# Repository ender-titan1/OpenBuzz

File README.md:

# OpenBuzz
OpenBuzz is a free and open source buzzer system for trivia games & tournaments, gameshows, or any competition where timing matters. It can be used with 2 teams of up to 4 players or with up to 8 independent players.

## Features
- Open source 
- Fully hand-solderable
- Modular and modifyable
- Designed to be fabricated as cheaply as possible
- Support for extensive customization, many game modes and a wide range of buzzer sounds
- Use of common RJ45 connector for easy and cheap connection between base and pods

## Why make this?
Professional buzzer systems tend to be very expensive and not very customizable, as well as being tricky to obtain due to overseas shipping. OpenBuzz aims to provide a cheaper and more flexible alternative, while maintaining fairness and accurate winner detection. It was originally designed for a local trivia team that needed a system to practice with, but since has been made open source. As a bonus it allows players to have their own custom buzzers, ranging from simple buttons to way over-the-top triggers.

# Usage
1. Download schematic and PCB files
2. Modify freely to fit your needs, components, etc...
3. Fabricate with any online service for as little as <$10
4. Assemble base and as many pods as you need
5. 3D-print enclosures if needed
6. Use in any game you need it for!

**Disclaimer: V1 is included in this repository for historical reference only. Versions V2 and above are the ones intended for use.**

PCB files and schematics are provided as KiCad files. 3D files for enclosures are provided as STEP files.

# License
The code and firmware included in the `src` folder is covered by the GNU General Public License v3.0, while the design files (schematics, PCB layout, 3D models) in the `hardware` folder are covered by the CERN Open Hardware Licence Version 2 - Strongly Reciprocal license. The full license texts can be found in their respective folders.

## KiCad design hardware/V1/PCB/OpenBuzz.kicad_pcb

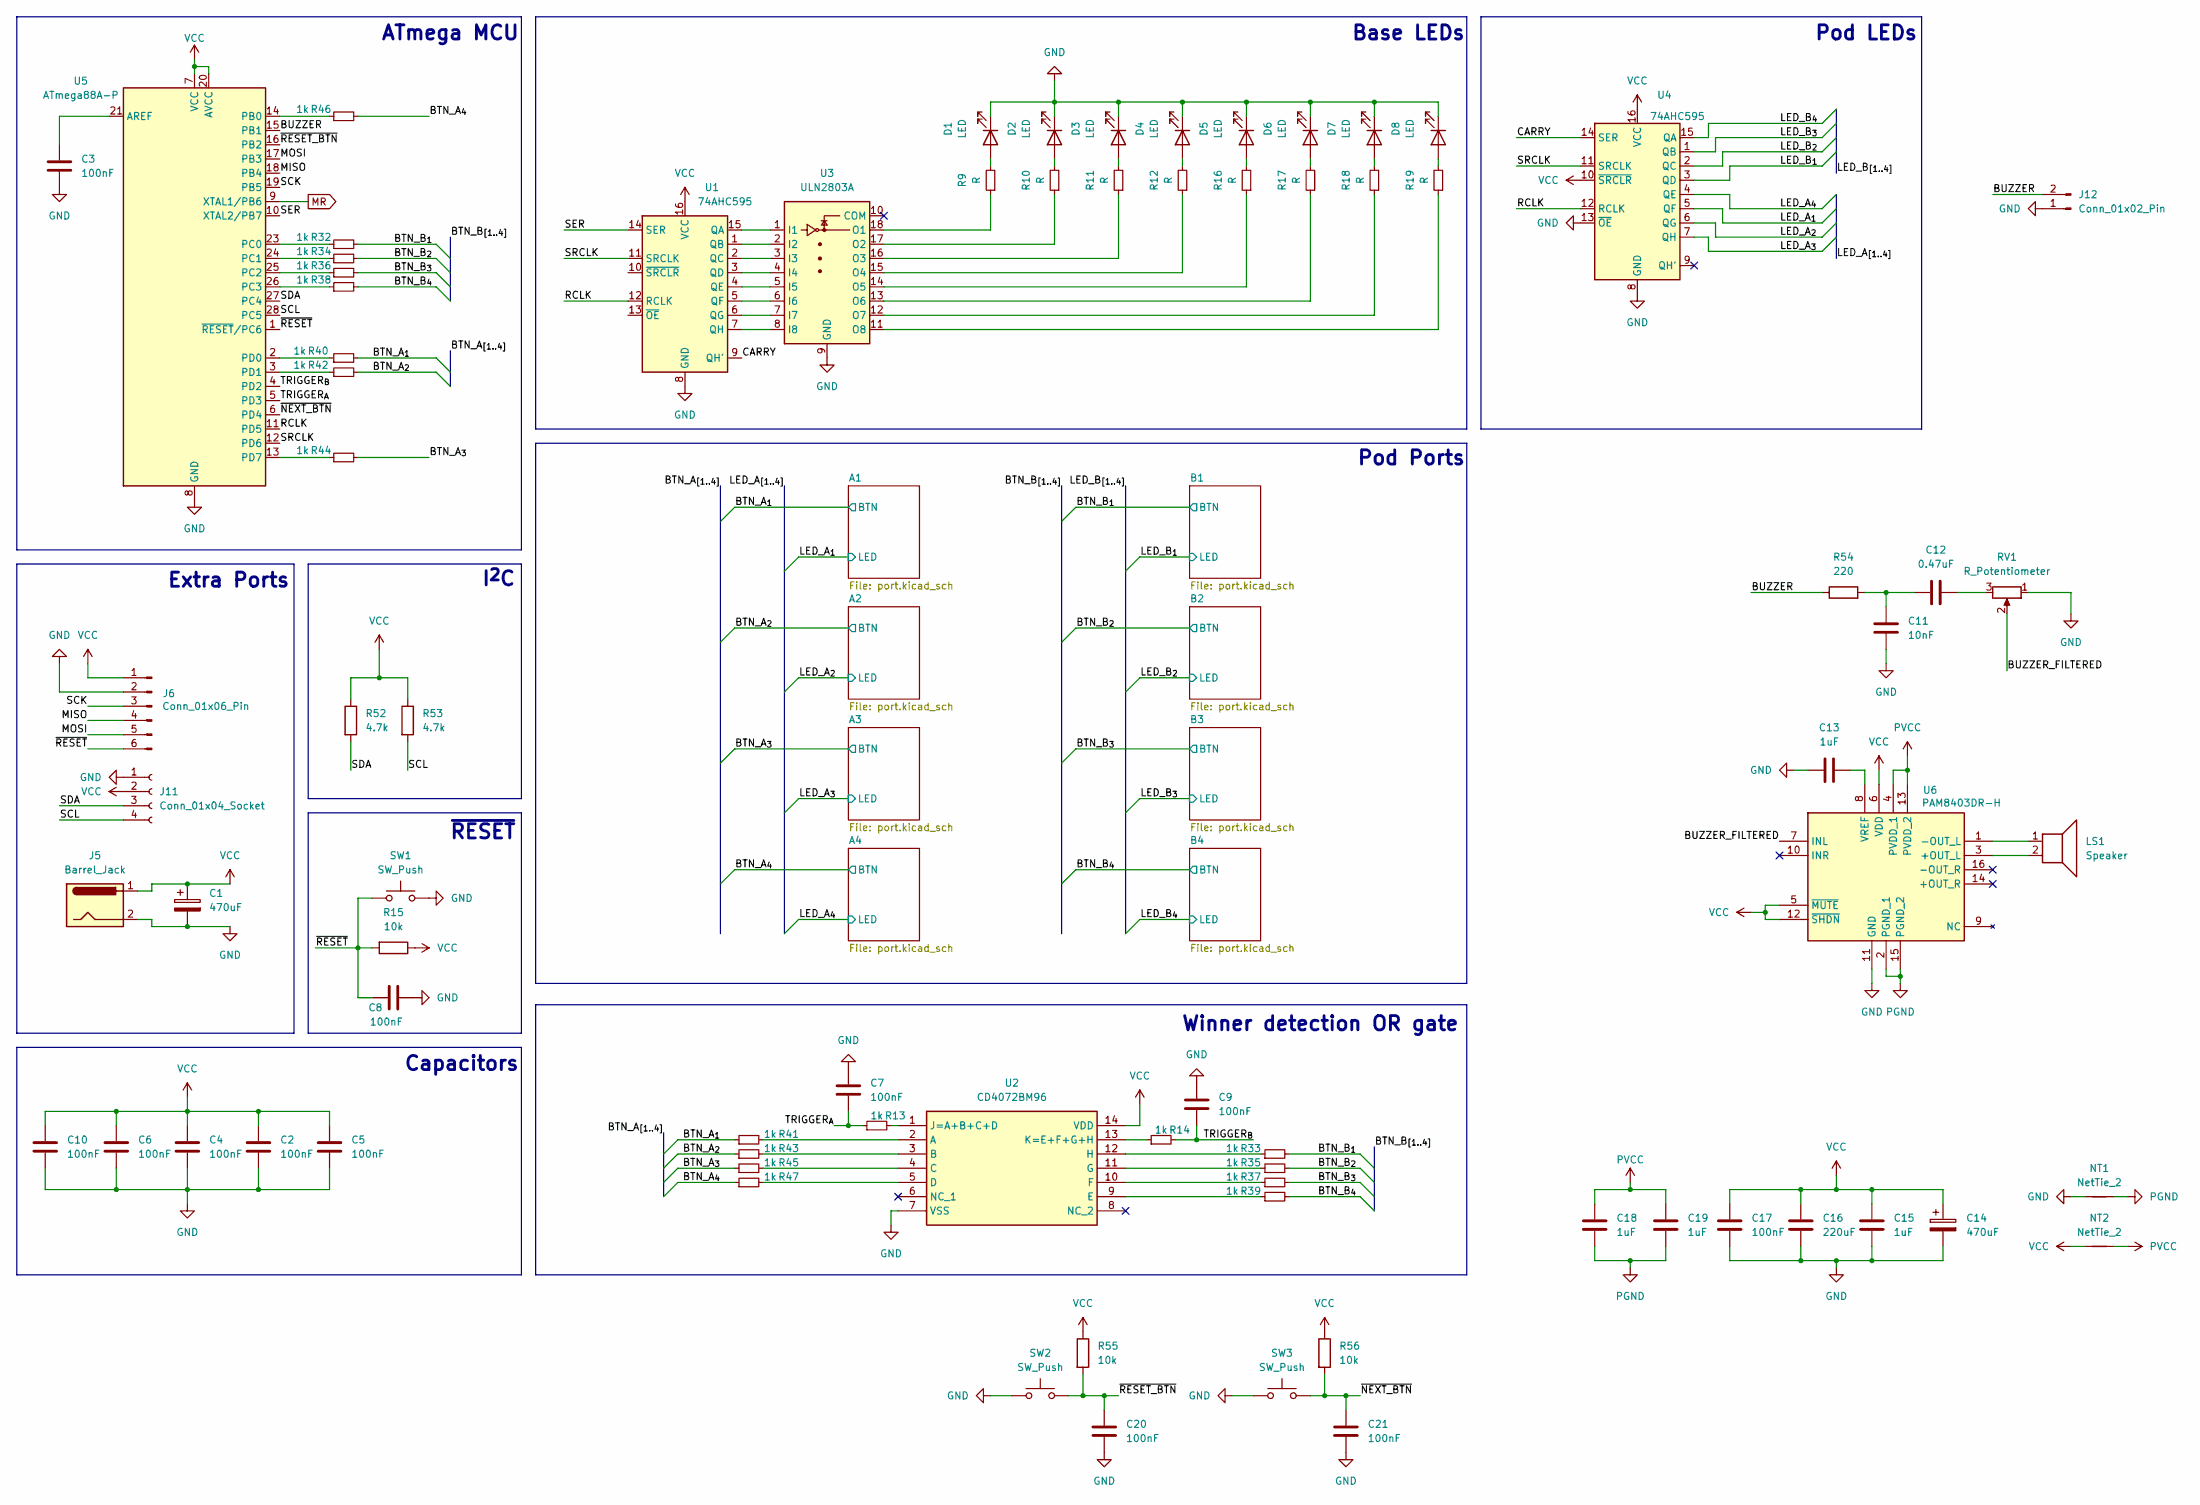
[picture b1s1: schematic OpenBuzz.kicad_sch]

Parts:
C1, C14: 470uF; CP_Radial_D8.0mm_P3.50mm
C2, C3, C4, C5, C6, C7, C8, C9, C10, C17, C20, C21: 100nF; C_0805_2012Metric_Pad1.18x1.45mm_HandSolder
C11: 10nF; C_0805_2012Metric_Pad1.18x1.45mm_HandSolder
C12: 0.47uF; C_0805_2012Metric_Pad1.18x1.45mm_HandSolder
C13, C15, C18, C19: 1uF; C_0805_2012Metric_Pad1.18x1.45mm_HandSolder
C16: 220uF; C_0805_2012Metric_Pad1.18x1.45mm_HandSolder
D1, D2, D3, D4, D5, D6, D7, D8: LED; LED_D5.0mm
J5: Barrel_Jack; BarrelJack_Horizontal
J6: Conn_01x06_Pin; PinHeader_1x06_P2.54mm_Vertical
J11: Conn_01x04_Socket; NS-Tech_Grove_1x04_P2mm_Vertical
J12: Conn_01x02_Pin; PinHeader_1x02_P2.54mm_Vertical
LS1: Speaker; PinHeader_1x02_P2.54mm_Vertical
NT1, NT2: NetTie_2; NetTie-2_SMD_Pad2.0mm
R9, R10, R11, R12, R16, R17, R18, R19: R; R_0805_2012Metric_Pad1.20x1.40mm_HandSolder
R13, R14, R32, R33, R34, R35, R36, R37, R38, R39, R40, R41, R42, R43, R44, R45, R46, R47: 1k; R_0805_2012Metric_Pad1.20x1.40mm_HandSolder
R15, R55, R56: 10k; R_0805_2012Metric_Pad1.20x1.40mm_HandSolder
R52, R53: 4.7k; R_0805_2012Metric_Pad1.20x1.40mm_HandSolder
R54: 220; R_0805_2012Metric_Pad1.20x1.40mm_HandSolder
RV1: R_Potentiometer; PinHeader_1x03_P2.54mm_Vertical
SW1: SW_Push; SW_Push_1P1T_NO_CK_KSC6xxJ
SW2, SW3: SW_Push; PinHeader_1x02_P2.54mm_Vertical
U1, U4: 74AHC595; DIP-16_W7.62mm_Socket_LongPads
U2: CD4072BM96; SOIC-14_3.9x8.7mm_P1.27mm; Mouser Part Number 595-CD4072BE
U3: ULN2803A; DIP-18_W7.62mm_Socket_LongPads
U5: ATmega88A-P; DIP-28_W7.62mm_Socket_LongPads
U6: PAM8403DR-H; SOIC-16_3.9x9.9mm_P1.27mm; Manufacturer_Part_Number PAM8403DR-H

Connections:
/BTN_A_{1}: R40.2, R41.1; also elsewhere on the board
/BTN_A_{2}: R42.2, R43.1; also elsewhere on the board
/BTN_A_{3}: R44.2, R45.1; also elsewhere on the board
/BTN_A_{4}: R46.2, R47.1; also elsewhere on the board
/BTN_B_{1}: R32.2, R33.2; also elsewhere on the board
/BTN_B_{2}: R34.2, R35.2; also elsewhere on the board
/BTN_B_{3}: R36.2, R37.2; also elsewhere on the board
/BTN_B_{4}: R38.2, R39.2; also elsewhere on the board
/BUZZER: J12.2, R54.1, U5.15 (PB1)
/BUZZER_FILTERED: RV1.2, U6.7 (INL)
/CARRY: U1.9 (QH'), U4.14 (SER)
/LED_A_{1}: U4.5 (QF); also elsewhere on the board
/LED_A_{2}: U4.6 (QG); also elsewhere on the board
/LED_A_{3}: U4.7 (QH); also elsewhere on the board
/LED_A_{4}: U4.4 (QE); also elsewhere on the board
/LED_B_{1}: U4.3 (QD); also elsewhere on the board
/LED_B_{2}: U4.2 (QC); also elsewhere on the board
/LED_B_{3}: U4.1 (QB); also elsewhere on the board
/LED_B_{4}: U4.15 (QA); also elsewhere on the board
/MISO: J6.4, U5.18 (PB4)
/MOSI: J6.5, U5.17 (PB3)
/RCLK: U1.12 (RCLK), U4.12 (RCLK), U5.11 (PD5)
/SCK: J6.3, U5.19 (PB5)
/SCL: J11.4, R53.2, U5.28 (PC5)
/SDA: J11.3, R52.2, U5.27 (PC4)
/SER: U1.14 (SER), U5.10 (XTAL2/PB7)
/SRCLK: U1.11 (SRCLK), U4.11 (SRCLK), U5.12 (PD6)
/TRIGGER_{A}: C7.2, R13.1, U5.5 (PD3)
/TRIGGER_{B}: C9.2, R14.2, U5.4 (PD2)
/~NEXT_BTN: C21.1, R56.2, SW3.2, U5.6 (PD4)
/~RESET_BTN: C20.1, R55.2, SW2.2, U5.16 (PB2)
/~RESET: C8.2, J6.6, R15.2, SW1.1, U5.1 (~RESET/PC6)
GND: C1.2, C2.2, C3.2, C4.2, C5.2, C6.2, C7.1, C8.1, C9.1, C10.2, C11.2, C13.1, C14.2, C15.2, C16.2, C17.2, C20.2, C21.2, D1.1 (K), D2.1 (K), D3.1 (K), D4.1 (K), D5.1 (K), D6.1 (K), D7.1 (K), D8.1 (K), J5.2, J6.2, J11.1, J12.1, NT1.1, RV1.1, SW1.2, SW2.1, SW3.1, U1.8 (GND), U2.7 (VSS), U3.9 (GND), U4.8 (GND), U4.13 (~OE), U5.8 (GND), U5.22 (GND), U6.11 (GND); also elsewhere on the board
MR: U5.9 (XTAL1/PB6); also elsewhere on the board
unnamed: C11.1, C12.1, R54.2
unnamed: C12.2, RV1.3
unnamed: D1.2 (A), R9.2
unnamed: D2.2 (A), R10.2
unnamed: D3.2 (A), R11.2
unnamed: D4.2 (A), R12.2
unnamed: D5.2 (A), R16.2
unnamed: D6.2 (A), R17.2
unnamed: D7.2 (A), R18.2
unnamed: D8.2 (A), R19.2
unnamed: U1.15 (QA), U3.1 (I1)
unnamed: U1.1 (QB), U3.2 (I2)
unnamed: U1.2 (QC), U3.3 (I3)
unnamed: U1.3 (QD), U3.4 (I4)
unnamed: U1.4 (QE), U3.5 (I5)
unnamed: U1.5 (QF), U3.6 (I6)
unnamed: U1.6 (QG), U3.7 (I7)
unnamed: U1.7 (QH), U3.8 (I8)
unnamed: R41.2, U2.2 (A)
unnamed: R43.2, U2.3 (B)
unnamed: R45.2, U2.4 (C)
unnamed: R47.2, U2.5 (D)
unnamed: R39.1, U2.9 (E)
unnamed: R37.1, U2.10 (F)
unnamed: R35.1, U2.11 (G)
unnamed: R33.1, U2.12 (H)
unnamed: R13.2, U2.1 (J=A+B+C+D)
unnamed: R14.1, U2.13 (K=E+F+G+H)
unnamed: R9.1, U3.18 (O1)
unnamed: R10.1, U3.17 (O2)
unnamed: R11.1, U3.16 (O3)
unnamed: R12.1, U3.15 (O4)
unnamed: R16.1, U3.14 (O5)
unnamed: R17.1, U3.13 (O6)
unnamed: R18.1, U3.12 (O7)
unnamed: R19.1, U3.11 (O8)
unnamed: C3.1, U5.21 (AREF)
unnamed: R46.1, U5.14 (PB0)
unnamed: R32.1, U5.23 (PC0)
unnamed: R34.1, U5.24 (PC1)
unnamed: R36.1, U5.25 (PC2)
unnamed: R38.1, U5.26 (PC3)
unnamed: R40.1, U5.2 (PD0)
unnamed: R42.1, U5.3 (PD1)
unnamed: R44.1, U5.13 (PD7)
unnamed: LS1.2, U6.3 (+OUT_L)
unnamed: LS1.1, U6.1 (-OUT_L)
unnamed: C13.2, U6.8 (VREF)
PGND: C18.2, C19.2, NT1.2, U6.2 (PGND_1), U6.15 (PGND_2)
PVCC: C18.1, C19.1, NT2.2, U6.4 (PVDD_1), U6.13 (PVDD_2)
VCC: C1.1, C2.1, C4.1, C5.1, C6.1, C10.1, C14.1, C15.1, C16.1, C17.1, J5.1, J6.1, J11.2, NT2.1, R15.1, R52.1, R53.1, R55.1, R56.1, U1.16 (VCC), U2.14 (VDD), U4.10 (~SRCLR), U4.16 (VCC), U5.7 (VCC), U5.20 (AVCC), U6.5 (~MUTE), U6.6 (VDD), U6.12 (~SHDN); also elsewhere on the board

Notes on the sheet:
Base LEDs
~{RESET}
Pod LEDs
ATmega MCU
Pod Ports
I^{2}C
Extra Ports
Capacitors
Winner detection OR gate

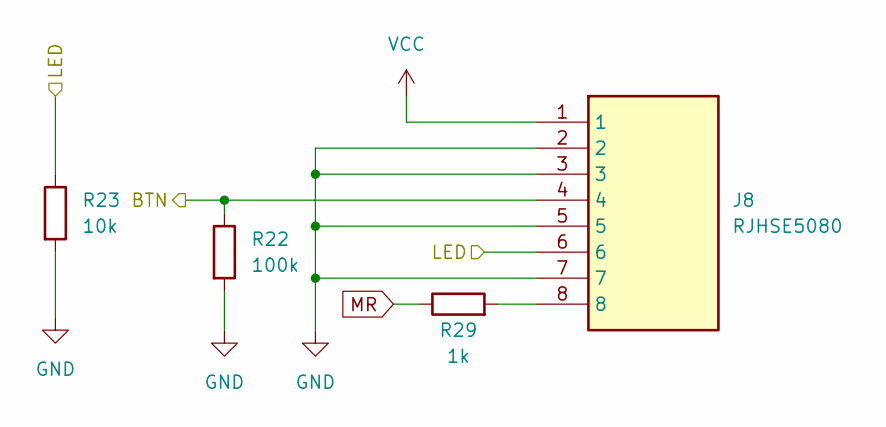
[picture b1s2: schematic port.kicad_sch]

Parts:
J8: RJHSE5080; Manufacturer_Part_Number RJHSE5080
R22: 100k; R_0805_2012Metric_Pad1.20x1.40mm_HandSolder
R23: 10k; R_0805_2012Metric_Pad1.20x1.40mm_HandSolder
R29: 1k; R_0805_2012Metric_Pad1.20x1.40mm_HandSolder

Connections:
/BTN_B_{2}: J8.4, R22.1; also elsewhere on the board
/LED_B_{2}: J8.6, R23.1; also elsewhere on the board
GND: J8.2, J8.3, J8.5, J8.7, R22.2, R23.2; also elsewhere on the board
MR: R29.1; also elsewhere on the board
unnamed: J8.8, R29.2
VCC: J8.1; also elsewhere on the board

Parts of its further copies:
J1, J2, J3, J4, J7, J9, J10: RJHSE5080; Manufacturer_Part_Number RJHSE5080
R1, R3, R5, R7, R21, R25, R27: 10k; R_0805_2012Metric_Pad1.20x1.40mm_HandSolder
R2, R4, R6, R8, R20, R24, R26: 100k; R_0805_2012Metric_Pad1.20x1.40mm_HandSolder
R28, R30, R31, R48, R49, R50, R51: 1k; R_0805_2012Metric_Pad1.20x1.40mm_HandSolder

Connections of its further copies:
/BTN_A_{1}: J1.4, R2.1; also elsewhere on the board
/BTN_A_{2}: J2.4, R4.1; also elsewhere on the board
/BTN_A_{3}: J3.4, R6.1; also elsewhere on the board
/BTN_A_{4}: J4.4, R8.1; also elsewhere on the board
/BTN_B_{1}: J7.4, R20.1; also elsewhere on the board
/BTN_B_{3}: J9.4, R24.1; also elsewhere on the board
/BTN_B_{4}: J10.4, R26.1; also elsewhere on the board
/LED_A_{1}: J1.6, R1.1; also elsewhere on the board
/LED_A_{2}: J2.6, R3.1; also elsewhere on the board
/LED_A_{3}: J3.6, R5.1; also elsewhere on the board
/LED_A_{4}: J4.6, R7.1; also elsewhere on the board
/LED_B_{1}: J7.6, R21.1; also elsewhere on the board
/LED_B_{3}: J9.6, R25.1; also elsewhere on the board
/LED_B_{4}: J10.6, R27.1; also elsewhere on the board
GND: J1.2, J1.3, J1.5, J1.7, J2.2, J2.3, J2.5, J2.7, J3.2, J3.3, J3.5, J3.7, J4.2, J4.3, J4.5, J4.7, J7.2, J7.3, J7.5, J7.7, J9.2, J9.3, J9.5, J9.7, J10.2, J10.3, J10.5, J10.7, R1.2, R2.2, R3.2, R4.2, R5.2, R6.2, R7.2, R8.2, R20.2, R21.2, R24.2, R25.2, R26.2, R27.2; also elsewhere on the board
MR: R28.1, R30.1, R31.1, R48.1, R49.1, R50.1, R51.1; also elsewhere on the board
unnamed: J1.8, R48.2
unnamed: J2.8, R49.2
unnamed: J3.8, R50.2
unnamed: J4.8, R51.2
unnamed: J7.8, R28.2
unnamed: J9.8, R30.2
unnamed: J10.8, R31.2
VCC: J1.1, J2.1, J3.1, J4.1, J7.1, J9.1, J10.1; also elsewhere on the board

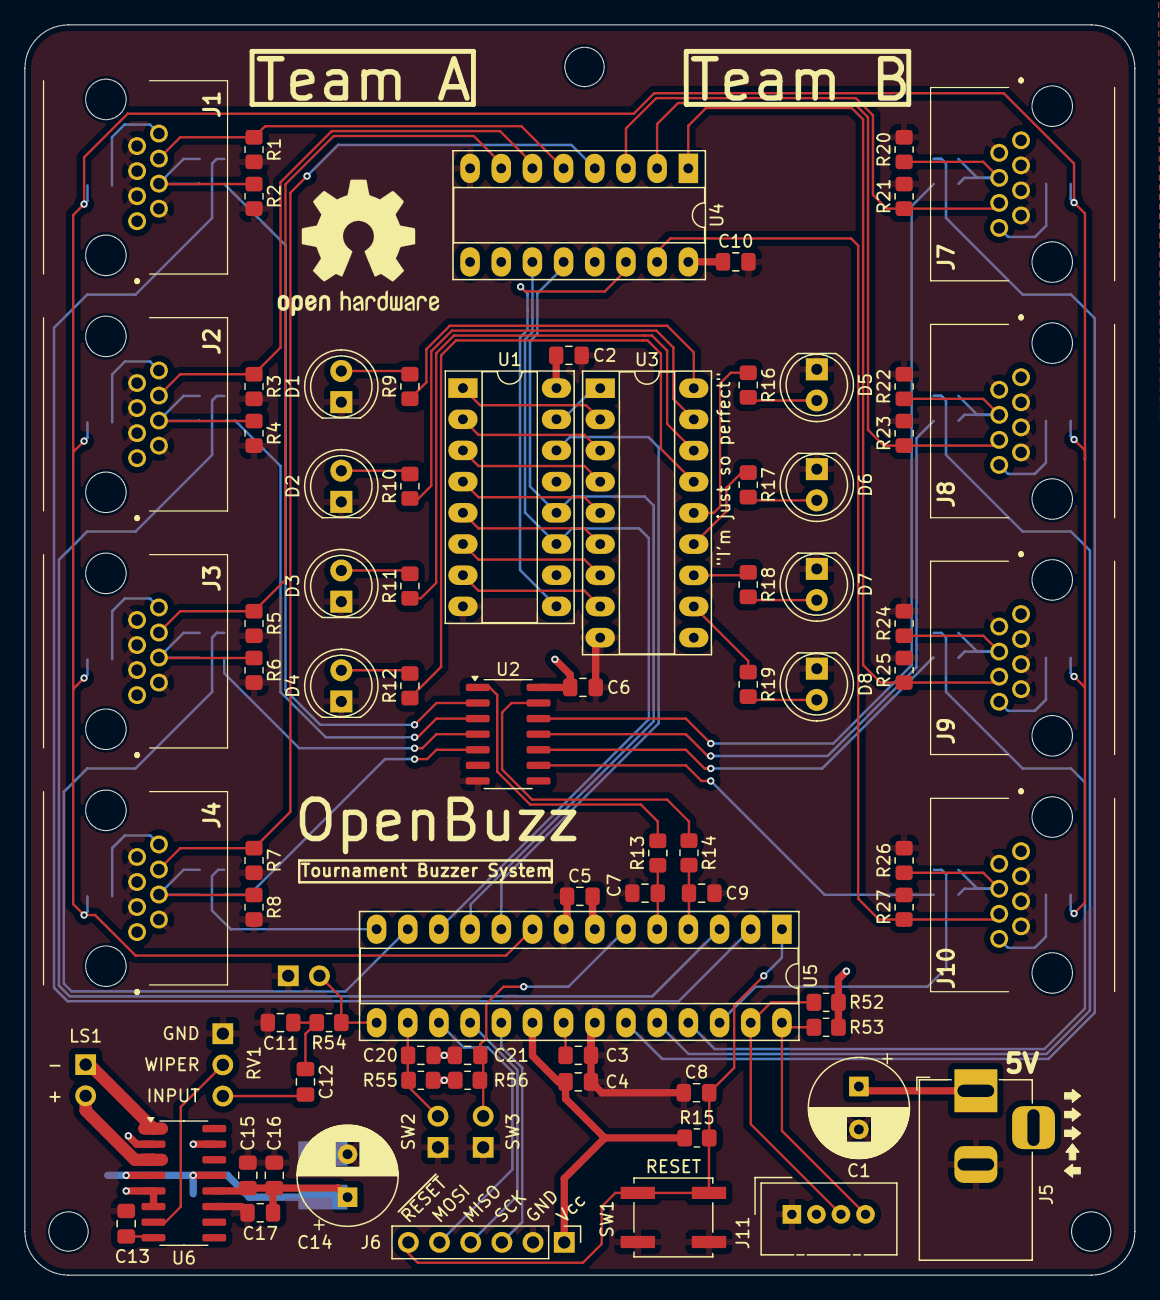
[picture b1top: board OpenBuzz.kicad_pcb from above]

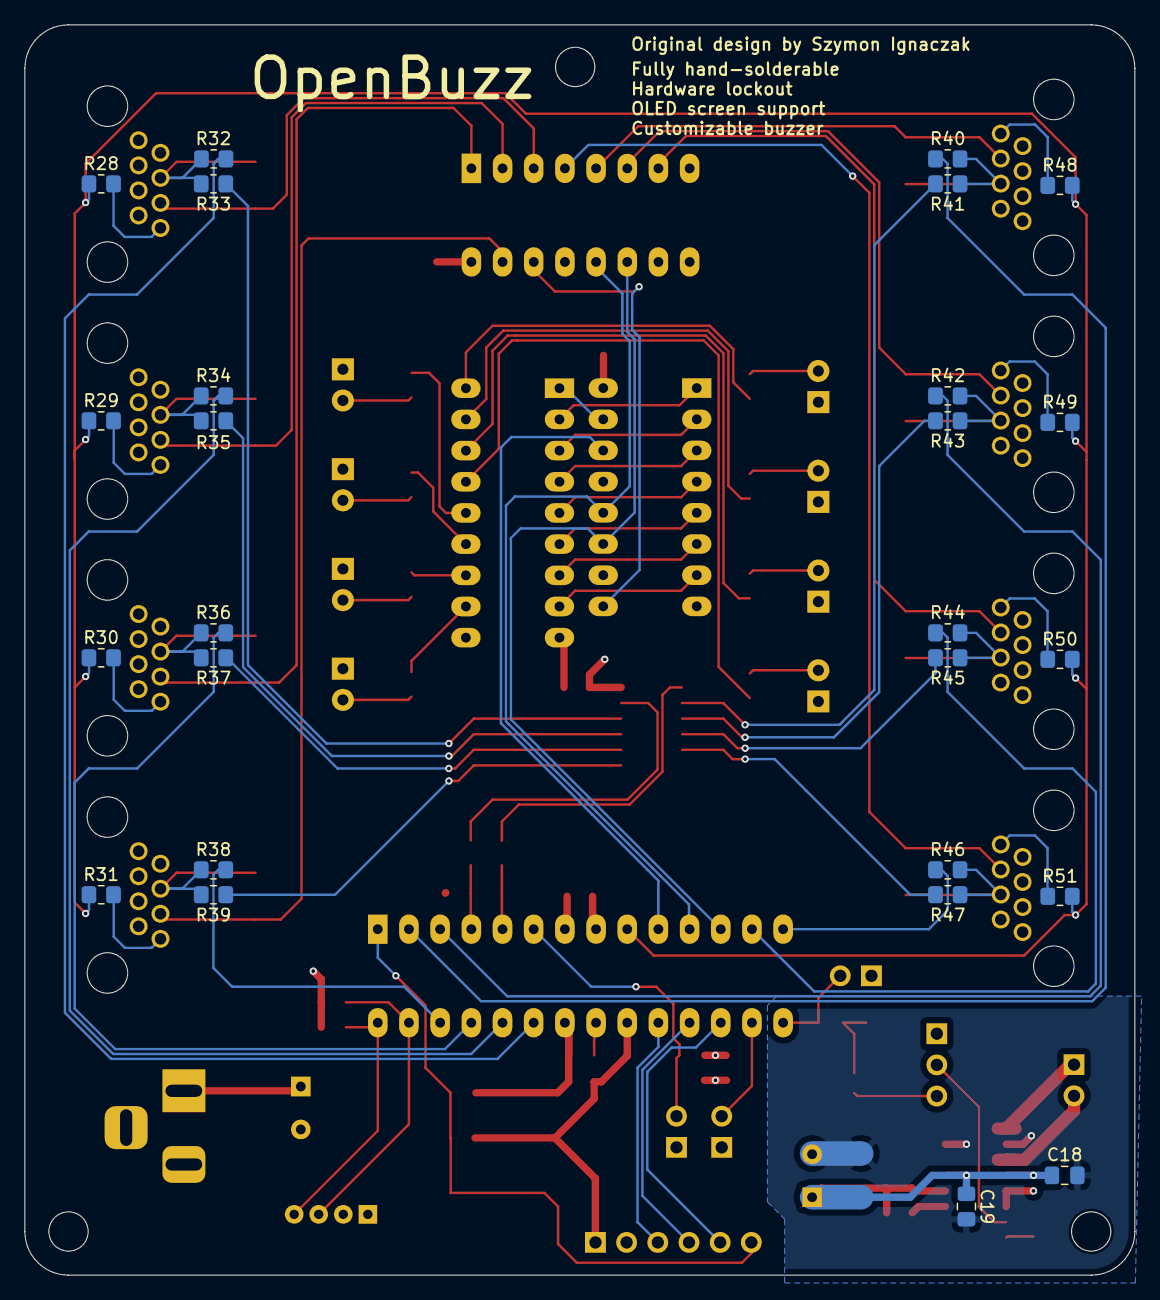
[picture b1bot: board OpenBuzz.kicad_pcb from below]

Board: 4 copper layers, 90.4 x 101.9 mm, 110 parts (28 on the bottom side), 93 nets.

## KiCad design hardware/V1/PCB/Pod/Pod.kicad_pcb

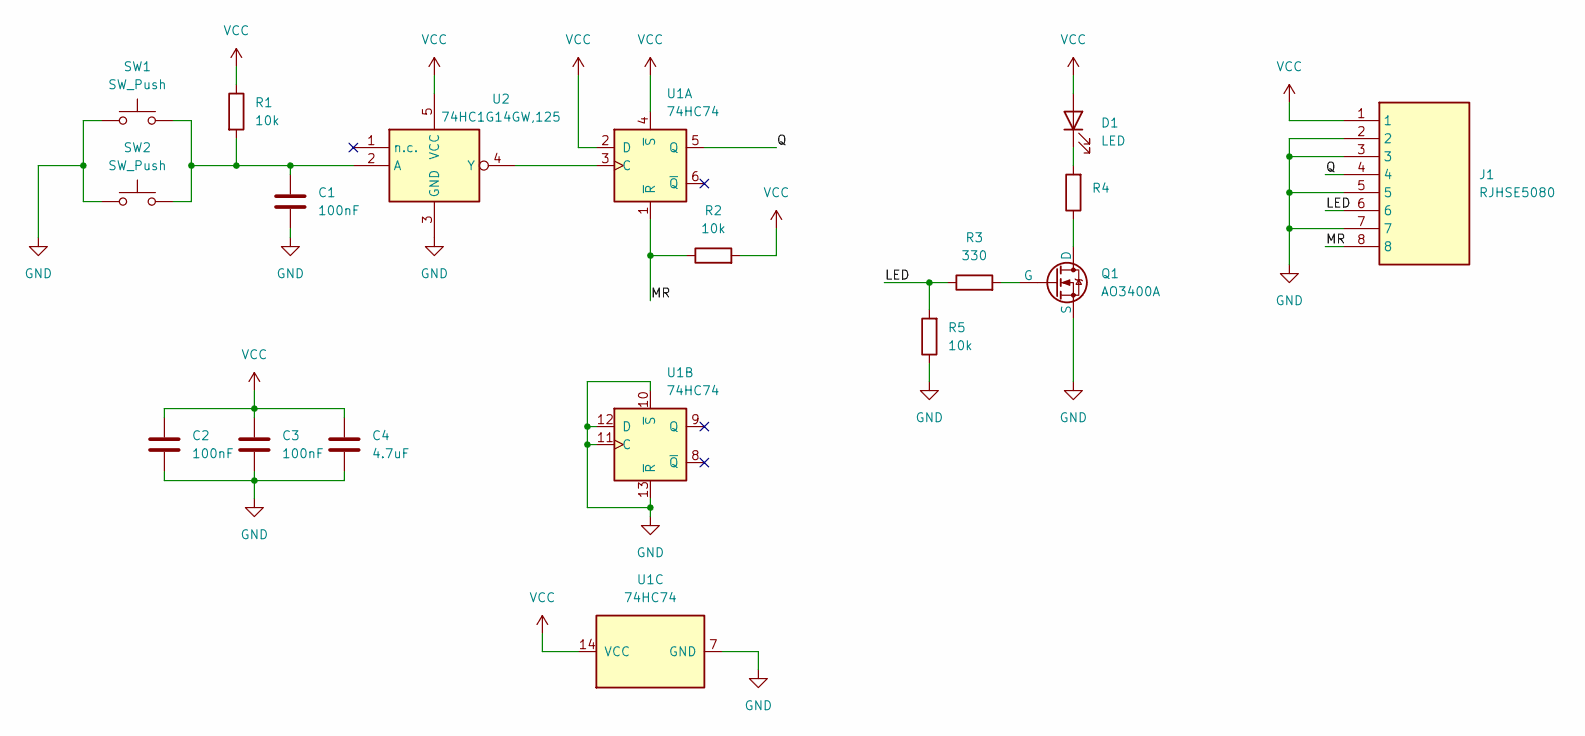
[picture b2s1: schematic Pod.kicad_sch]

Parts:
C1, C2, C3: 100nF; C_0805_2012Metric_Pad1.18x1.45mm_HandSolder
C4: 4.7uF; C_0805_2012Metric_Pad1.18x1.45mm_HandSolder
D1: LED; LED_D5.0mm
J1: RJHSE5080; Manufacturer_Part_Number RJHSE5080
Q1: AO3400A; SOT-23_Handsoldering
R1, R2, R5: 10k; R_0805_2012Metric_Pad1.20x1.40mm_HandSolder
R3: 330; R_0805_2012Metric_Pad1.20x1.40mm_HandSolder
R4: R_0805_2012Metric_Pad1.20x1.40mm_HandSolder
SW1: SW_Push; PinHeader_1x02_P2.54mm_Vertical
SW2: SW_Push; SW_Push_1P1T_NO_CK_KSC6xxJ
U1: 74HC74; SOIC-14_3.9x8.7mm_P1.27mm
U2: 74HC1G14GW,125; SOT-23-5_HandSoldering; Manufacturer_Part_Number 74HC1G14GW,125

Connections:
/LED: J1.6, R3.1, R5.2
/MR: J1.8, R2.1, U1.1 (~R)
/Q: J1.4, U1.5 (Q)
GND: C1.1, C2.1, C3.1, C4.2, J1.2, J1.3, J1.5, J1.7, Q1.3 (S), R5.1, SW1.1, SW2.1, U1.7 (GND), U1.10 (~S), U1.11 (C), U1.12 (D), U1.13 (~R), U2.3 (GND)
unnamed: D1.1 (K), R4.2
unnamed: Q1.1 (D), R4.1
unnamed: Q1.2 (G), R3.2
unnamed: U1.3 (C), U2.4 (Y)
unnamed: C1.2, R1.2, SW1.2, SW2.2, U2.2 (A)
VCC: C2.2, C3.2, C4.1, D1.2 (A), J1.1, R1.1, R2.2, U1.2 (D), U1.4 (~S), U1.14 (VCC), U2.5 (VCC)

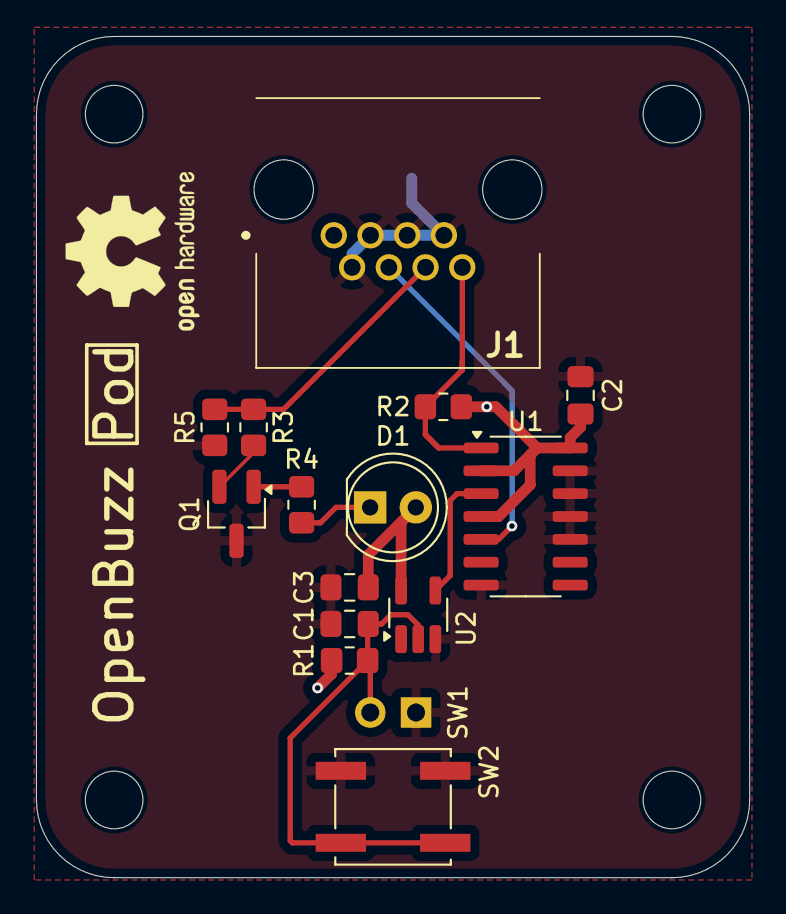
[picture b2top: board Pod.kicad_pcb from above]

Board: 2 copper layers, 39.6 x 46.7 mm, 16 parts (1 on the bottom side), 10 nets.

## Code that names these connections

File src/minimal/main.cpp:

#include <stdint.h>
#include "Arduino.h"
#include "avr/io.h"

// Minimal Version of the controller script for OpenBuzz V1:
//    - Winner detection
//    - Tone generation (with piezo buzzer on pin 9)
//    - Master reset

// MCU pins
#define SER 21
#define SRCLK 6
#define RCLK 5
#define MR 20       // Active LOW 
#define BUZZER 9
#define RST_BTN 10  // Active LOW

// Teams
#define TEAM_A 0
#define TEAM_B 1
#define NO_TEAM 0xFF

// Tones
#define TEAM_A_TONE 3500
#define TEAM_B_TONE 3300
#define TONE_DURATION_MS 300

// Player input pins
#define A1 PB0
#define A2 PD1
#define A3 PD7
#define A4 PD0

#define B1 PC0
#define B2 PC1
#define B3 PC2
#define B4 PC3

uint8_t pod_led_lookup_team_a[] = {
  0b00000000,
  0b00100000,
  0b01000000,
  0b10000000,
  0b00010000,
};

// Status variables
volatile uint8_t team_buzzed = NO_TEAM;
volatile bool buzzed = false;
bool handled = false;

// Input buffer
volatile uint8_t snapshotB;
volatile uint8_t snapshotC;
volatile uint8_t snapshotD;

void initMCU() {
  // Set all pins as inputs unless overriden
  DDRB = 0x00;
  DDRC = 0x00;
  DDRD = 0x00;

  pinMode(SER, OUTPUT);
  pinMode(SRCLK, OUTPUT);
  pinMode(RCLK, OUTPUT);
  pinMode(MR, OUTPUT);
  pinMode(BUZZER, OUTPUT);

  digitalWrite(MR, true);
}

void initInterrputs() {
  pinMode(2, INPUT); // INT0 / TEAM B
  pinMode(3, INPUT); // INT1 / TEAM A

  EIMSK |= _BV(INT0) | _BV(INT1); // Enable INT0 and INT1
  EICRA = 0b00001111; // Trigger both on rising edge (ISC = 0b11)

  sei();
}

void shift(uint16_t output) {
  digitalWrite(RCLK, false);
  shiftOut(SER, SRCLK, MSBFIRST, output >> 8);
  shiftOut(SER, SRCLK, MSBFIRST, output & 0xFF);
  digitalWrite(RCLK, true);
}

void selectLED(uint8_t team, uint8_t player) {
  uint8_t base_LEDs = (1 << (player - 1 + team * 4));
  uint8_t pod_LEDs = 0x00;
  
  if (team == TEAM_B)
    pod_LEDs = (1 << (4 - player + !team * 4));
  else
    pod_LEDs = pod_led_lookup_team_a[player];

  uint16_t output = (pod_LEDs << 8) + base_LEDs;

  shift(output);
}

void clearLED() {
  shift(0x0000);
}

void resetBuzzers() {
  digitalWrite(MR, false);
  delay(1);
  digitalWrite(MR, true);

  clearLED();
  buzzed = false;
  handled = false;
  team_buzzed = NO_TEAM;
}

void handleBuzz() {
  uint8_t player = 0;

  if (team_buzzed == TEAM_A) {
    if (snapshotB & _BV(A1))
      player = 1;

    if (snapshotD & _BV(A2))
      player = 2;

    if (snapshotD & _BV(A3))
      player = 3;

    if (snapshotD & _BV(A4))
      player = 4;
    
    tone(BUZZER, TEAM_A_TONE, TONE_DURATION_MS);
  }

  if (team_buzzed == TEAM_B) {
    if (snapshotC & _BV(B1))
      player = 1;

    if (snapshotC & _BV(B2))
      player = 2;

    if (snapshotC & _BV(B3))
      player = 3;

    if (snapshotC & _BV(B4))
      player = 4;
  
    tone(BUZZER, TEAM_B_TONE, TONE_DURATION_MS);
  }

  selectLED(team_buzzed, player);
}

int main() {
  init();
  initMCU();
  initInterrputs();
  clearLED();

  while (true) {
    if (buzzed && !handled) {
      handleBuzz();
      handled = true;
    }

    if (!digitalRead(RST_BTN)) {
      resetBuzzers();
    }
  }
}

// Team B buzzed
ISR(INT0_vect) {
  if (!buzzed) {
    snapshotB = PINB;
    snapshotC = PINC;
    snapshotD = PIND;

    buzzed = true;
    team_buzzed = TEAM_B;
  }
}

// Team A buzzed
ISR(INT1_vect) {
  if (!buzzed) {
    snapshotB = PINB;
    snapshotC = PINC;
    snapshotD = PIND;

    buzzed = true;
    team_buzzed = TEAM_A;
  }
}

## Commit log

2026-02-23 Upload V1
